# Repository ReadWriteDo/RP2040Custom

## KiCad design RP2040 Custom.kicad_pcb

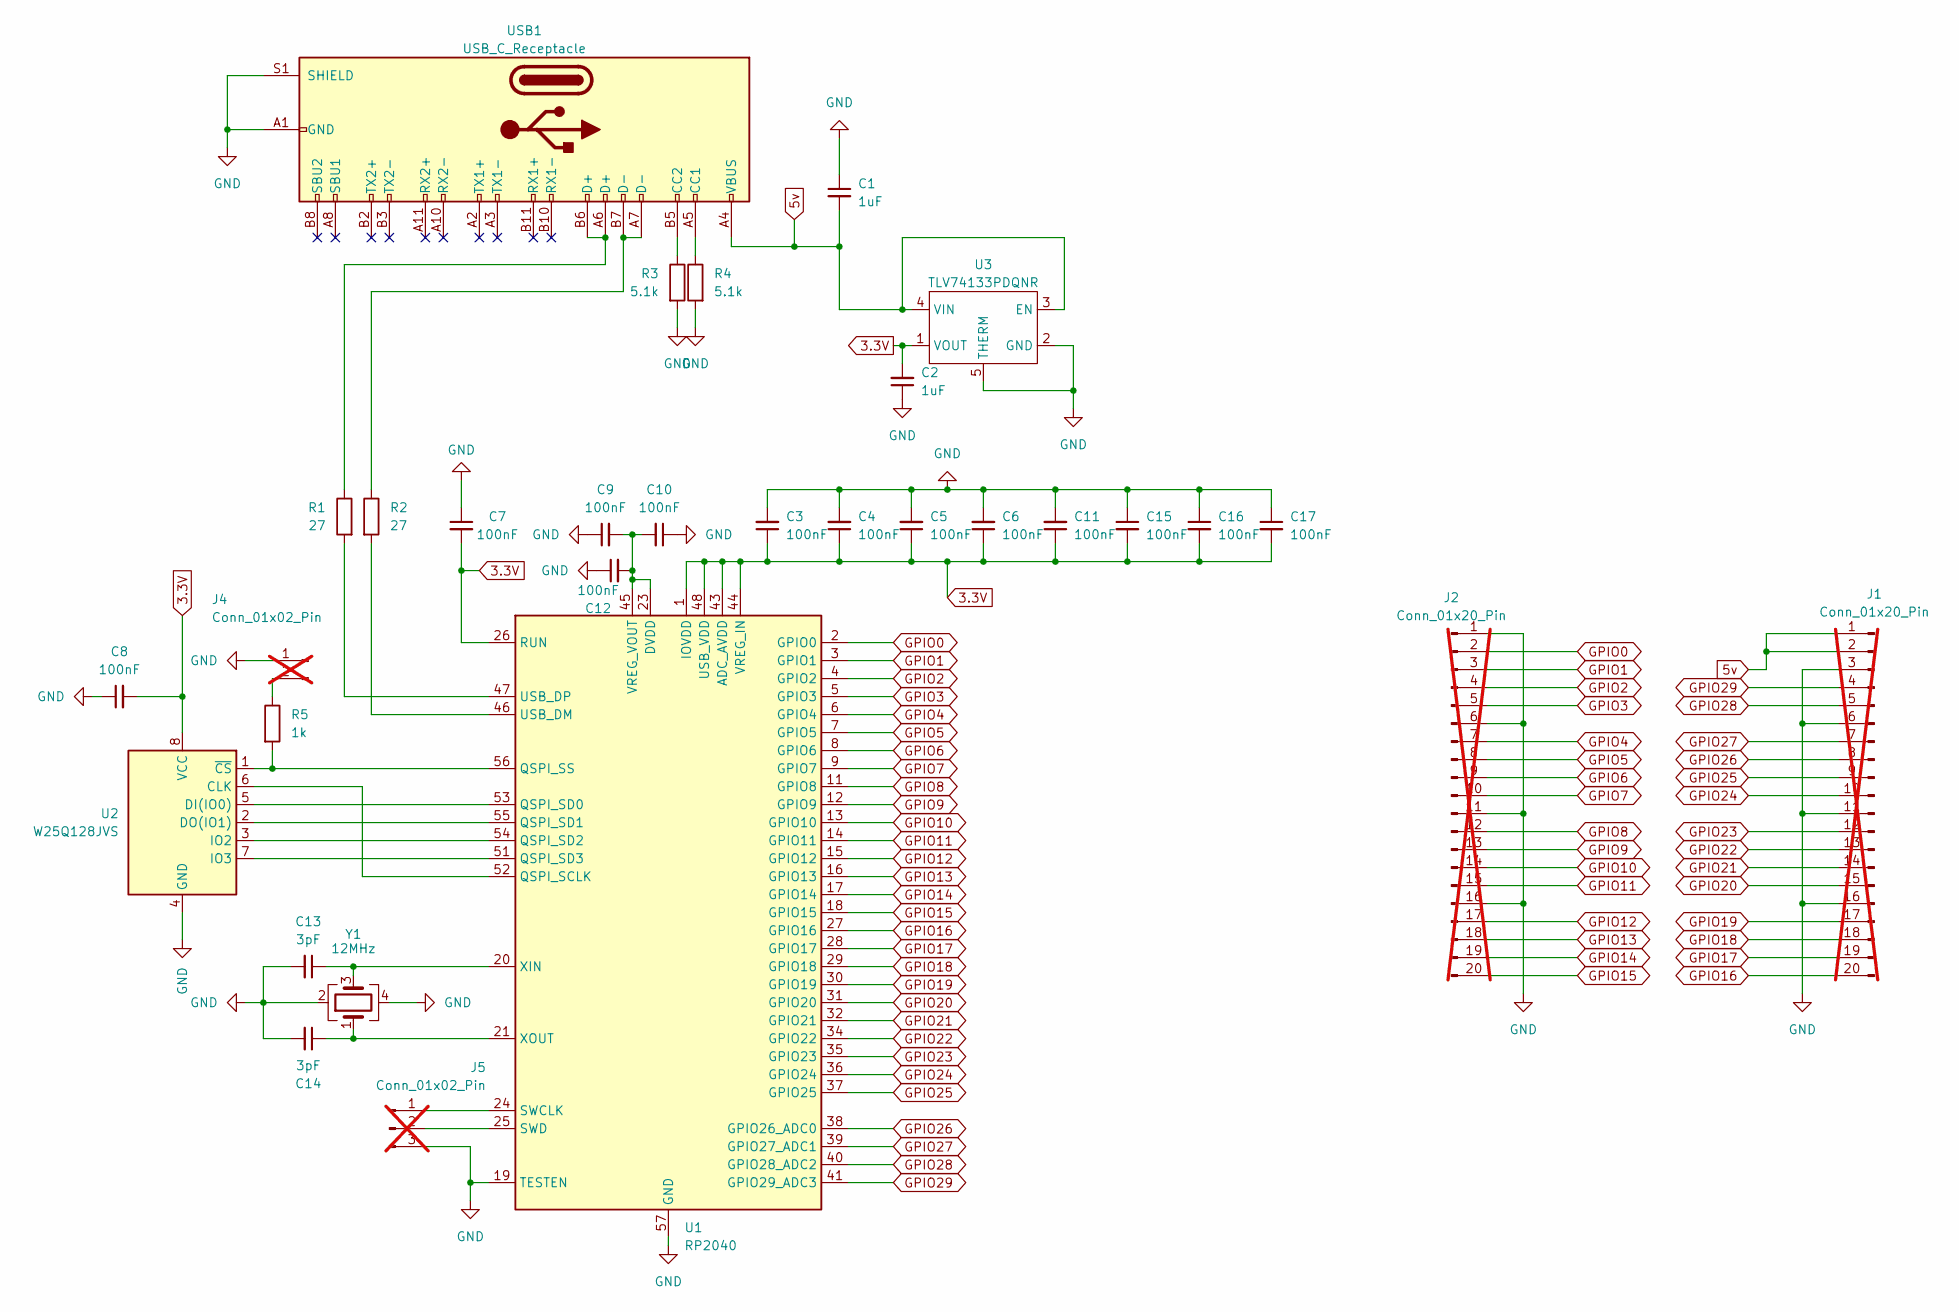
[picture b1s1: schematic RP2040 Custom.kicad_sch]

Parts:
C1, C2: 1uF; C_0603_1608Metric; LCSC C15849
C3, C4, C5, C6, C7, C8, C11: 100nF; C_0402_1005Metric; LCSC C159815
C9, C10, C12, C15, C16, C17: 100nF; C_0402_1005Metric
C13, C14: 3pF; C_0402_1005Metric
J1, J2: Conn_01x20_Pin; PinHeader_1x20_P2.54mm_Vertical; not fitted
J4: Conn_01x02_Pin; PinHeader_1x02_P2.54mm_Vertical; not fitted
J5: Conn_01x02_Pin; PinHeader_1x03_P2.54mm_Vertical; not fitted
R1, R2: 27; C_0201_0603Metric; LCSC C273295
R3, R4: 5.1k; R_0603_1608Metric; LCSC C403509
R5: 1k; R_0201_0603Metric
U1: RP2040; QFN-56-1EP_7x7mm_P0.4mm_EP3.2x3.2mm; LCSC C2040
U2: W25Q128JVS; SOIC-8_5.23x5.23mm_P1.27mm; LCSC C97521
U3: TLV74133PDQNR; Texas_X2SON-4_1x1mm_P0.65mm; LCSC C485136
USB1: USB_C_Receptacle; USB_C_Receptacle_G-Switch_GT-USB-7010ASV; LCSC C2988369
Y1: 12MHz; Crystal_SMD_3225-4Pin_3.2x2.5mm; LCSC C2933034

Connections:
3.3V: C2.2, C3.1, C4.1, C5.1, C6.1, C7.2, C8.2, C11.1, C15.2, C16.2, C17.2, U1.1 (IOVDD), U1.10 (IOVDD), U1.22 (IOVDD), U1.26 (RUN), U1.33 (IOVDD), U1.42 (IOVDD), U1.43 (ADC_AVDD), U1.44 (VREG_IN), U1.48 (USB_VDD), U1.49 (IOVDD), U2.8 (VCC), U3.1 (VOUT)
5v: C1.2, J1.1, J1.2, U3.3 (EN), U3.4 (VIN), USB1.A4 (VBUS), USB1.A9 (VBUS), USB1.B4 (VBUS), USB1.B9 (VBUS)
GND: C1.1, C2.1, C3.2, C4.2, C5.2, C6.2, C7.1, C8.1, C9.1, C10.1, C11.2, C12.1, C13.2, C14.2, C15.1, C16.1, C17.1, J1.3, J1.6, J1.11, J1.16, J2.1, J2.6, J2.11, J2.16, J4.1, J5.3, R3.2, R4.2, U1.19 (TESTEN), U1.57 (GND), U2.4 (GND), U3.2 (GND), U3.5 (THERM), USB1.A1 (GND), USB1.A12 (GND), USB1.B1 (GND), USB1.B12 (GND), USB1.S1 (SHIELD), Y1.2, Y1.4
GPIO0: J2.2, U1.2 (GPIO0)
GPIO1: J2.3, U1.3 (GPIO1)
GPIO2: J2.4, U1.4 (GPIO2)
GPIO3: J2.5, U1.5 (GPIO3)
GPIO4: J2.7, U1.6 (GPIO4)
GPIO5: J2.8, U1.7 (GPIO5)
GPIO6: J2.9, U1.8 (GPIO6)
GPIO7: J2.10, U1.9 (GPIO7)
GPIO8: J2.12, U1.11 (GPIO8)
GPIO9: J2.13, U1.12 (GPIO9)
GPIO10: J2.14, U1.13 (GPIO10)
GPIO11: J2.15, U1.14 (GPIO11)
GPIO12: J2.17, U1.15 (GPIO12)
GPIO13: J2.18, U1.16 (GPIO13)
GPIO14: J2.19, U1.17 (GPIO14)
GPIO15: J2.20, U1.18 (GPIO15)
GPIO16: J1.20, U1.27 (GPIO16)
GPIO17: J1.19, U1.28 (GPIO17)
GPIO18: J1.18, U1.29 (GPIO18)
GPIO19: J1.17, U1.30 (GPIO19)
GPIO20: J1.15, U1.31 (GPIO20)
GPIO21: J1.14, U1.32 (GPIO21)
GPIO22: J1.13, U1.34 (GPIO22)
GPIO23: J1.12, U1.35 (GPIO23)
GPIO24: J1.10, U1.36 (GPIO24)
GPIO25: J1.9, U1.37 (GPIO25)
GPIO26: J1.8, U1.38 (GPIO26_ADC0)
GPIO27: J1.7, U1.39 (GPIO27_ADC1)
GPIO28: J1.5, U1.40 (GPIO28_ADC2)
GPIO29: J1.4, U1.41 (GPIO29_ADC3)
unnamed: J4.2, R5.1
unnamed: J5.1, U1.24 (SWCLK)
unnamed: J5.2, U1.25 (SWD)
unnamed: U1.52 (QSPI_SCLK), U2.6 (CLK)
unnamed: U1.53 (QSPI_SD0), U2.5 (DI(IO0))
unnamed: U1.55 (QSPI_SD1), U2.2 (DO(IO1))
unnamed: U1.54 (QSPI_SD2), U2.3 (IO2)
unnamed: U1.51 (QSPI_SD3), U2.7 (IO3)
unnamed: R5.2, U1.56 (QSPI_SS), U2.1 (~CS)
unnamed: R2.2, U1.46 (USB_DM)
unnamed: R1.2, U1.47 (USB_DP)
unnamed: C9.2, C10.2, C12.2, U1.23 (DVDD), U1.45 (VREG_VOUT), U1.50 (DVDD)
unnamed: C13.1, U1.20 (XIN), Y1.3
unnamed: C14.1, U1.21 (XOUT), Y1.1
unnamed: R4.1, USB1.A5 (CC1)
unnamed: R3.1, USB1.B5 (CC2)
USB-D+: R1.1, USB1.A6 (D+), USB1.B6 (D+)
USB-D-: R2.1, USB1.A7 (D-), USB1.B7 (D-)

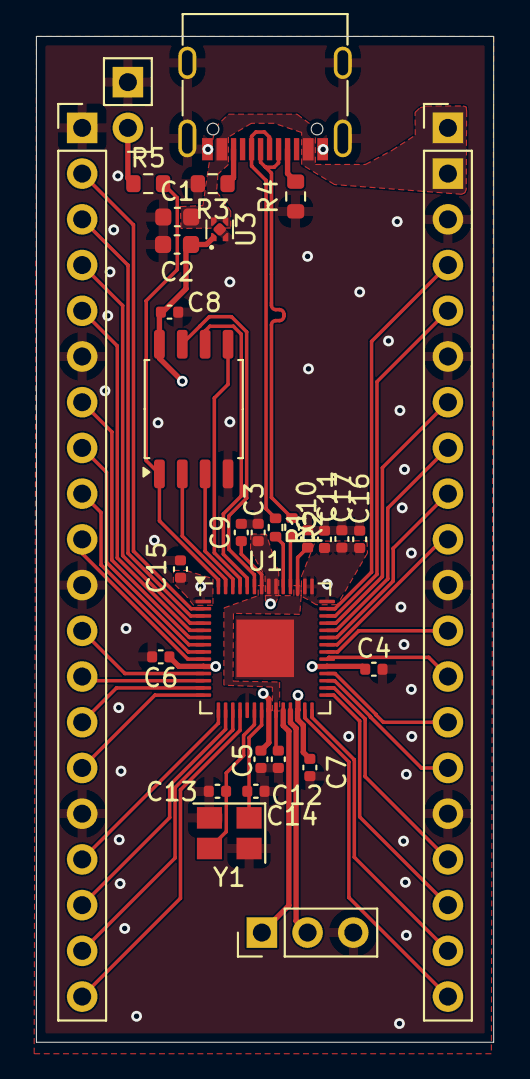
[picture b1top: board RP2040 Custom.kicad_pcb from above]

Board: 4 copper layers, 25.4 x 55.9 mm, 31 parts (0 on the bottom side), 51 nets.

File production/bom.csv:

Designator,Footprint,Quantity,Value,LCSC Part #
"C1, C2",0603,2,1uF,
"C10, C3, C4, C9",0402,4,100nF,C159815
"C11, C12, C15, C16, C17, C5, C6, C7, C8",0402,9,100nF,
"C13, C14",0402,2,3pF,
"R1, R2",0402,2,27,C966818
"R3, R4",0603,2,5.1k,C403509
R5,0603,1,1k,
U1,QFN-56-1EP_7x7mm_P0.4mm_EP3.2x3.2mm,1,RP2040,C2040
U2,SOIC-8_5.23x5.23mm_P1.27mm,1,W25Q128JVS,C97521
U3,Texas_X2SON-4_1x1mm_P0.65mm,1,TLV74133PDQNR,C485136
USB1,USB_C_Receptacle_G-Switch_GT-USB-7010ASV,1,USB_C_Receptacle,C2988369
Y1,Crystal_SMD_3225-4Pin_3.2x2.5mm,1,12MHz,C2933034

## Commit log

2024-08-03 v2 w/ better routing, power actually run where it needs to be, and thinner profile
2024-08-03 Removed redundant files
